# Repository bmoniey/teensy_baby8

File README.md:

# teensy_baby8
Music sequencer based on teensy3.2 micro

## 1. Features:

* 8 Steps, 32 divisions per step

* 8 Pots read on analog inputs. Each pot sets the values value of note for each step

* 8 Lighted buttons
	Lights to show which step is active
	Lights when button is pressed

## 2. Buttons:
	Regular Mode: Just to plays notes on a selected channel
	Skip Mode: Buttons cause sequencer to reset at the step of the pressed button

## 3. PCF8574
Uses PCF8574 IO expander to read buttons, drive LEDS and issue an interrupt when any of the input IO's change.
The design used 2 of the boards each driving 4 LEDS and reading 4 Buttons. The PCF8574 library is an adaptation of 
https://github.com/xreef/PCF8574_library

## 4. MIDI - This sequencer sends MIDI via serial port on Teensy 3.2
	Uses MIDI commands sent via serial to a program like Ableton Live.
	Needs a USB to MIDI adapter.

## 5. OLED Display SSD1306 128 x 64
* Used to provide menu interface to make changes to the behaviour of the sequencer
* Set BPM (beats per minute)
* Select MIDI channel
* Turn On/Off tracks
* Select Octave
* Set Note Velocity
* Select mode of operation for buttons

## 6. Encoder KY-40 (Amazon)
* Uses incremental encoder with push-button to navigate menu
* Custom class used to handle increment,decrement and push-button events.
provides tracker for position and direction, and interrupts.

## 7. Menu
Class which derives from the Adafruit SSD1306 and GFX Library for simple text based
menu system. Encoder moves focus up and down page. Depress button to select. While selected
the item can be manipulated. Changes take immediate effect!

If Adafruit libraries are not already installed in your arduino lib then see here:

https://github.com/adafruit/Adafruit_SSD1306
https://github.com/adafruit/Adafruit-GFX-Library

### 8 Menu Elements:

* Pages

* GotoItems: links to other pages

* ListItems: Items on a page that display as text strings

* IntItems: Items which control an integer number

* FloatItems: Items which control floating point numbers

## TODO:
1. Make Midi interface configurable so that the Teensy built in MIDI HID interface could be used. Would eliminate the need
for a MIDI interface. This project was tested using an inexpensive USB midi interface connected to a PC.
2. Add Gate and CV outs using the Teensy on-board DAC and digital IO.

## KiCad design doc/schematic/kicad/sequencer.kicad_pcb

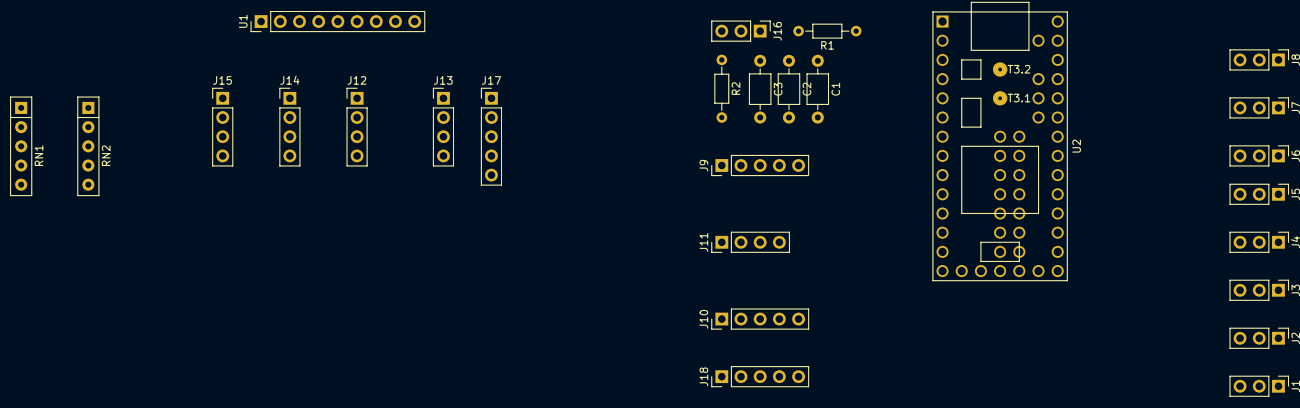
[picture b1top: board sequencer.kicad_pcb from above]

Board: 2 copper layers, 27 parts (0 on the bottom side), 28 nets, no tracks yet.

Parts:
C1, C2, C3: 0.1uF; C_Axial_L3.8mm_D2.6mm_P7.50mm_Horizontal
J1: POT1; PinHeader_1x03_P2.54mm_Vertical
J2: POT2; PinHeader_1x03_P2.54mm_Vertical
J3: POT3; PinHeader_1x03_P2.54mm_Vertical
J4: POT4; PinHeader_1x03_P2.54mm_Vertical
J5: POT5; PinHeader_1x03_P2.54mm_Vertical
J6: POT6; PinHeader_1x03_P2.54mm_Vertical
J7: POT7; PinHeader_1x03_P2.54mm_Vertical
J8: POT8; PinHeader_1x03_P2.54mm_Vertical
J9: ENC; PinHeader_1x05_P2.54mm_Vertical
J10: I2CBTN1; PinHeader_1x05_P2.54mm_Vertical
J11: I2CDSPLY; PinHeader_1x04_P2.54mm_Vertical
J12: BTN1; PinHeader_1x04_P2.54mm_Vertical
J13: BTN2; PinHeader_1x04_P2.54mm_Vertical
J14: BTN3; PinHeader_1x04_P2.54mm_Vertical
J15: BTN4; PinHeader_1x04_P2.54mm_Vertical
J16: MIDI_OUT; PinHeader_1x03_P2.54mm_Vertical
J17: I2C_BTNBD; PinHeader_1x05_P2.54mm_Vertical
J18: I2CBTN2; PinHeader_1x05_P2.54mm_Vertical
R1, R2: 33; R_Axial_DIN0204_L3.6mm_D1.6mm_P7.62mm_Horizontal
RN1: 470; R_Array_SIP5
RN2: 10K; R_Array_SIP5
U1: PCF8574; PinHeader_1x09_P2.54mm_Vertical
U2: Teensy3.2; Teensy30_31_32_LC

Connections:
3V3: J1.1, J2.1, J3.1, J4.1, J5.1, J6.1, J7.1, J8.1, J9.1, J10.1, J11.1, J17.1, J18.1, R2.2, RN1.1, RN2.1, U2.31
A0: J1.3, U2.21
A1: J2.3, U2.22
A2: J3.3, U2.23
A3: J4.3, U2.24
A6: J5.3, U2.27
A7: J6.3, U2.28
A8: J7.3, U2.29
A9: J8.3, U2.30
B0: J12.1, RN2.2, U1.4
B1: J13.1, RN2.3, U1.5
B2: J14.1, RN2.4, U1.6
B3: J15.1, U1.7
CLK: C1.2, J9.5, U2.6
DT: C3.2, J9.3, U2.4
GND: C1.1, C2.1, C3.1, J1.2, J2.2, J3.2, J4.2, J5.2, J6.2, J7.2, J8.2, J9.2, J10.2, J11.2, J12.2, J13.2, J14.2, J15.2, J16.2, J17.2, J18.2, U1.8, U2.1
INT: J10.5, J17.5, J18.5, U2.7
LD0: J12.3, U1.9
LDR0: J12.4, RN1.2
LDR1: J13.4, RN1.3
LDR2: J14.4, RN1.4
LDR3: J15.4, RN1.5
unnamed: J16.1, R1.2
unnamed: J16.3, R2.1
SCL: J10.4, J11.4, J17.3, J18.4, U2.26
SDA: J10.3, J11.3, J17.4, J18.3, U2.25
SW: C2.2, J9.4, U2.5
TX: R1.1, U2.3

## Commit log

2018-10-28 Intial Commit of docs and src
2018-10-29 added some pics of the cardboard prototype
2018-10-29 Added pdf print of BOM
2018-10-29 updated reamde
